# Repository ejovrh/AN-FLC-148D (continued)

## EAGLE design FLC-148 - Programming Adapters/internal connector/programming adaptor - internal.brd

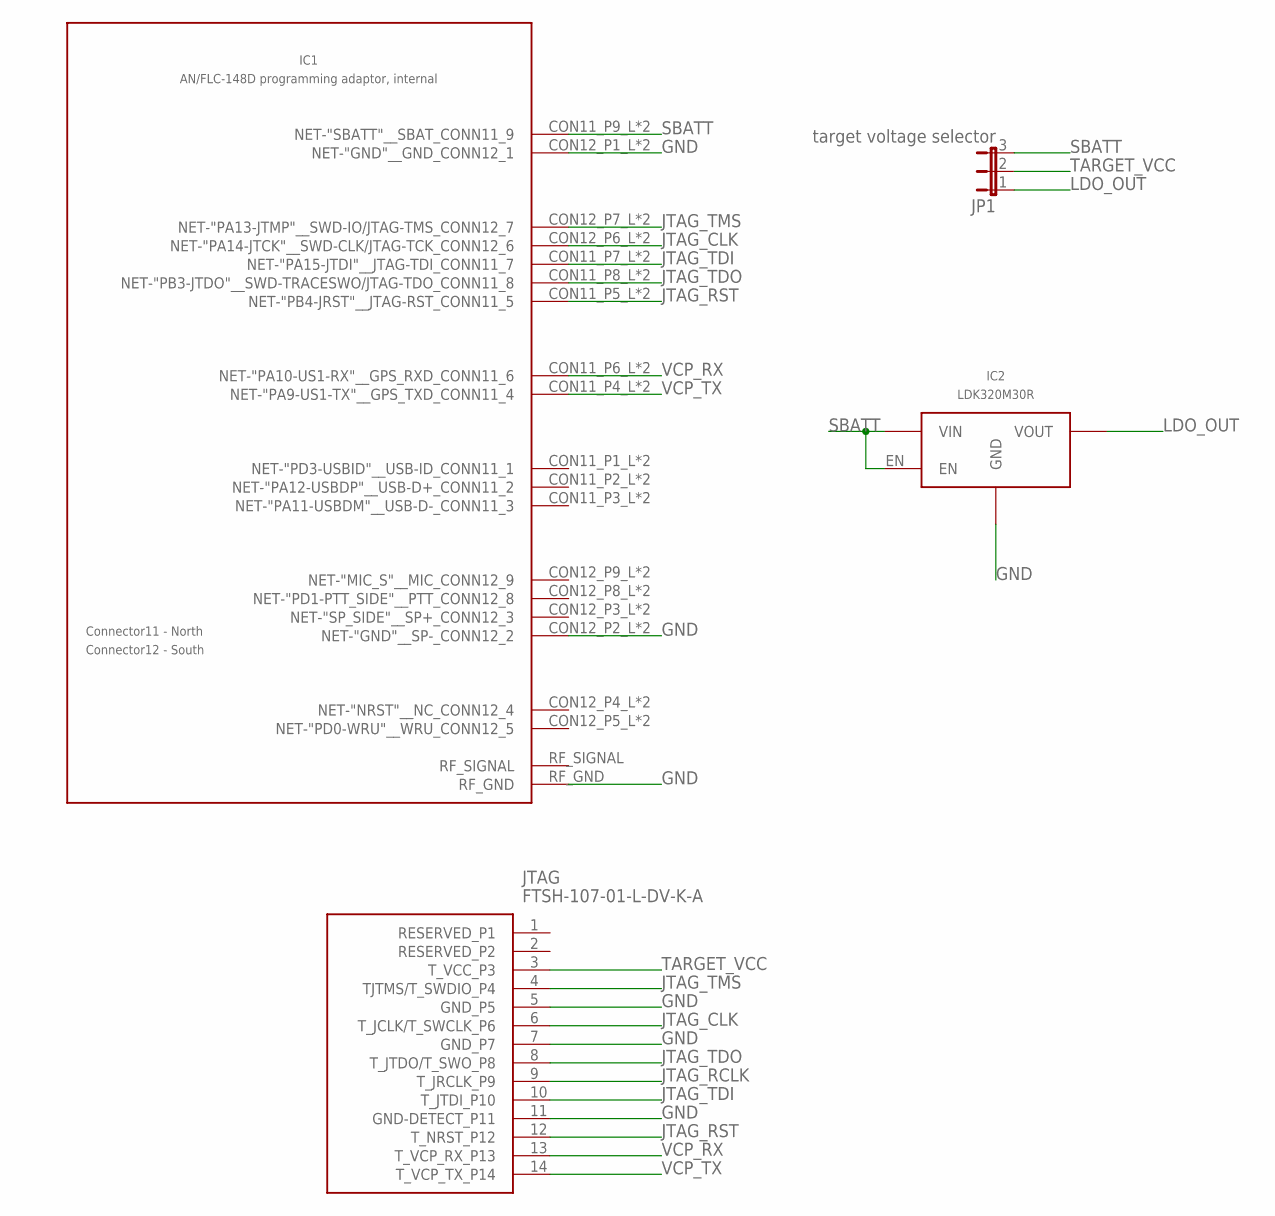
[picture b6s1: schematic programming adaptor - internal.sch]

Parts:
IC1: AN/FLC-148D programming adaptor, internal; INTERNAL_CONNECTOR
IC2: LDK320M30R; SOT-23-5L
JP1: target voltage selector; JP2
JTAG: FTSH-107-01-L-DV-K-A; FTSH10701LDVKA

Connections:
GND: IC1.CON12_P1_L (NET-"GND"__GND_CONN12_1), IC1.CON12_P1_R (NET-"GND"__GND_CONN12_1), IC1.CON12_P2_L (NET-"GND"__SP-_CONN12_2), IC1.CON12_P2_R (NET-"GND"__SP-_CONN12_2), IC1.RF_GND, IC2.GND, JTAG.5 (GND_P5), JTAG.7 (GND_P7), JTAG.11 (GND-DETECT_P11)
JTAG_CLK: IC1.CON12_P6_L (NET-"PA14-JTCK"__SWD-CLK/JTAG-TCK_CONN1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), IC1.CON12_P6_R (NET-"PA14-JTCK"__SWD-CLK/JTAG-TCK_CONN1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), JTAG.6 (T_JCLK/T_SWCLK_P6)
JTAG_RCLK: JTAG.9 (T_JRCLK_P9)
JTAG_RST: IC1.CON11_P5_L (NET-"PB4-JRST"__JTAG-RST_CONN11_5), IC1.CON11_P5_R (NET-"PB4-JRST"__JTAG-RST_CONN11_5), JTAG.12 (T_NRST_P12)
JTAG_TDI: IC1.CON11_P7_L (NET-"PA15-JTDI"__JTAG-TDI_CONN11_7), IC1.CON11_P7_R (NET-"PA15-JTDI"__JTAG-TDI_CONN11_7), JTAG.10 (T_JTDI_P10)
JTAG_TDO: IC1.CON11_P8_L (NET-"PB3-JTDO"__SWD-TRACESWO/JTAG-TDO_C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), IC1.CON11_P8_R (NET-"PB3-JTDO"__SWD-TRACESWO/JTAG-TDO_C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), JTAG.8 (T_JTDO/T_SWO_P8)
JTAG_TMS: IC1.CON12_P7_L (NET-"PA13-JTMP"__SWD-IO/JTAG-TMS_CONN12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), IC1.CON12_P7_R (NET-"PA13-JTMP"__SWD-IO/JTAG-TMS_CONN12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), JTAG.4 (TJTMS/T_SWDIO_P4)
LDO_OUT: IC2.OUT (VOUT), JP1.1
SBATT: IC1.CON11_P9_L (NET-"SBATT"__SBAT_CONN11_9), IC1.CON11_P9_R (NET-"SBATT"__SBAT_CONN11_9), IC2.EN, IC2.IN (VIN), JP1.3
TARGET_VCC: JP1.2, JTAG.3 (T_VCC_P3)
VCP_RX: IC1.CON11_P6_L (NET-"PA10-US1-RX"__GPS_RXD_CONN11_6), IC1.CON11_P6_R (NET-"PA10-US1-RX"__GPS_RXD_CONN11_6), JTAG.13 (T_VCP_RX_P13)
VCP_TX: IC1.CON11_P4_L (NET-"PA9-US1-TX"__GPS_TXD_CONN11_4), IC1.CON11_P4_R (NET-"PA9-US1-TX"__GPS_TXD_CONN11_4), JTAG.14 (T_VCP_TX_P14)

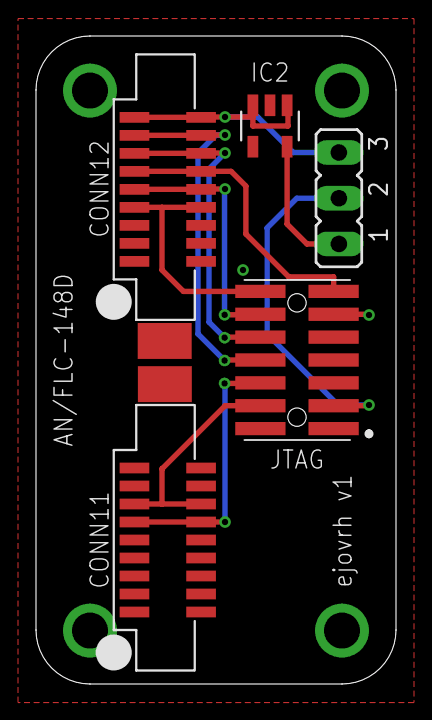
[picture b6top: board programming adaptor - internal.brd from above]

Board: 2 copper layers, 20.0 x 36.0 mm, 4 parts (0 on the bottom side), 11 nets.

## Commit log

2020-08-02 initial commit, contains already developed hardware
2020-08-02 renamed filename typo
2020-08-04 start of rev.2 board - the LCD D/C signal wasn't routed - pulldown resistors are likely needed for LED gate control - boot0 likely needs to be tied to GND
2020-08-08 start of rev.2 board: - replaced existing tact pushbuttons with lower profile ones
2020-08-08 - moved FFC solder pad south to correct for cable orientation
2020-08-08 start of rev.2 board
2020-08-08 - routed missing LCD D/C pin to PA12
2020-08-08 - renamed signals to be more consistent
2020-08-08 - replaced 1mm 5p zif connector (52793-0570) with better part (52207-0533)
2020-08-08 - started to remove 10k resistor arrays since pullups in the stm32 can replace them
2020-08-18 - removed R7 (swdclk to gnd), since it is not needed
2020-10-11 - connected rotary encoder A and B out directly to micro controller (previously these lines were going through the debouncing IC)
2020-10-11 - added todo/pin annotations where needed
2020-10-11 - more todo updates - added ground vias
2020-10-18 - renamed pins to be in sync with HW test script
2020-10-18 - added 10k pulldown to gate pins of illumination FETs, still needs routing
2020-10-22 - added exti conflict todo note
2020-10-29 - renamed MCU_KEYPAD_INTERRUPT to MCU_TO_KEYPAD_INT - in schematic added button names for LED associated with a button
